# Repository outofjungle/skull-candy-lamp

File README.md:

# Skull Candy Lamp

Replacement guts for the [Cute Skull Lamp](https://www.printables.com/model/40977-cute-skull-lamp).

## Front

## Back

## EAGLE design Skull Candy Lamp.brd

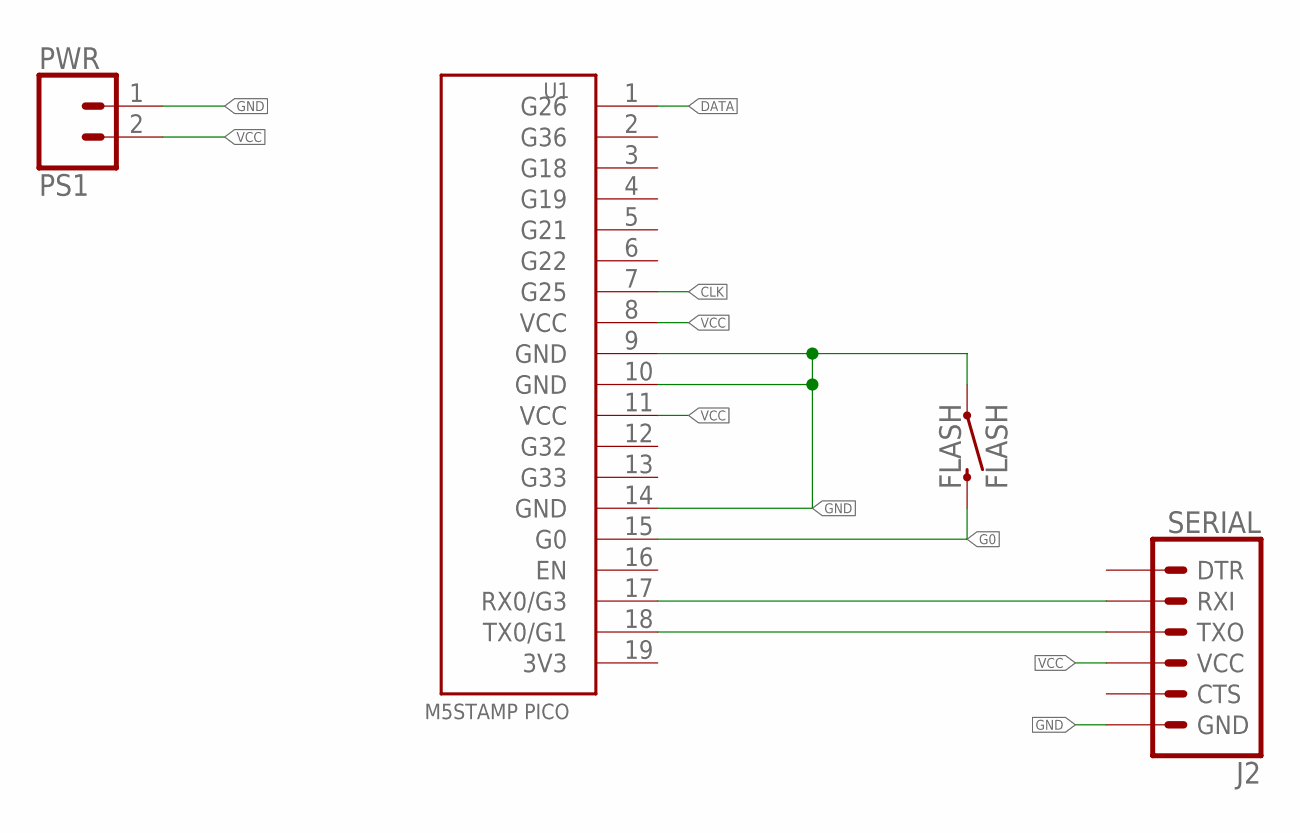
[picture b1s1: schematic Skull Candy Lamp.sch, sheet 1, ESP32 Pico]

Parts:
FLASH: FLASH; TACTILE_SWITCH_SMD_5.2MM
J2: SERIAL; 6_PIN_SERIAL_TARGET_SIDE_W_SILK
PS1: PWR; MOLEX-1X2_LOCK
U1: M5STAMP PICO; M5STAMP-PICO

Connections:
3V3: U1.19 (3V3)
CLK: U1.7 (G25); also elsewhere on the board
DATA: U1.1 (G26); also elsewhere on the board
G0: FLASH.3 (2), U1.15 (G0)
GND: FLASH.1, J2.P$6 (GND), PS1.1, U1.9 (GND), U1.10 (GND), U1.14 (GND); also elsewhere on the board
RX: J2.P$3 (RXI), U1.17 (RX0/G3)
TX: J2.P$2 (TXO), U1.18 (TX0/G1)
VCC: J2.P$4 (VCC), PS1.2, U1.8 (VCC), U1.11 (VCC); also elsewhere on the board

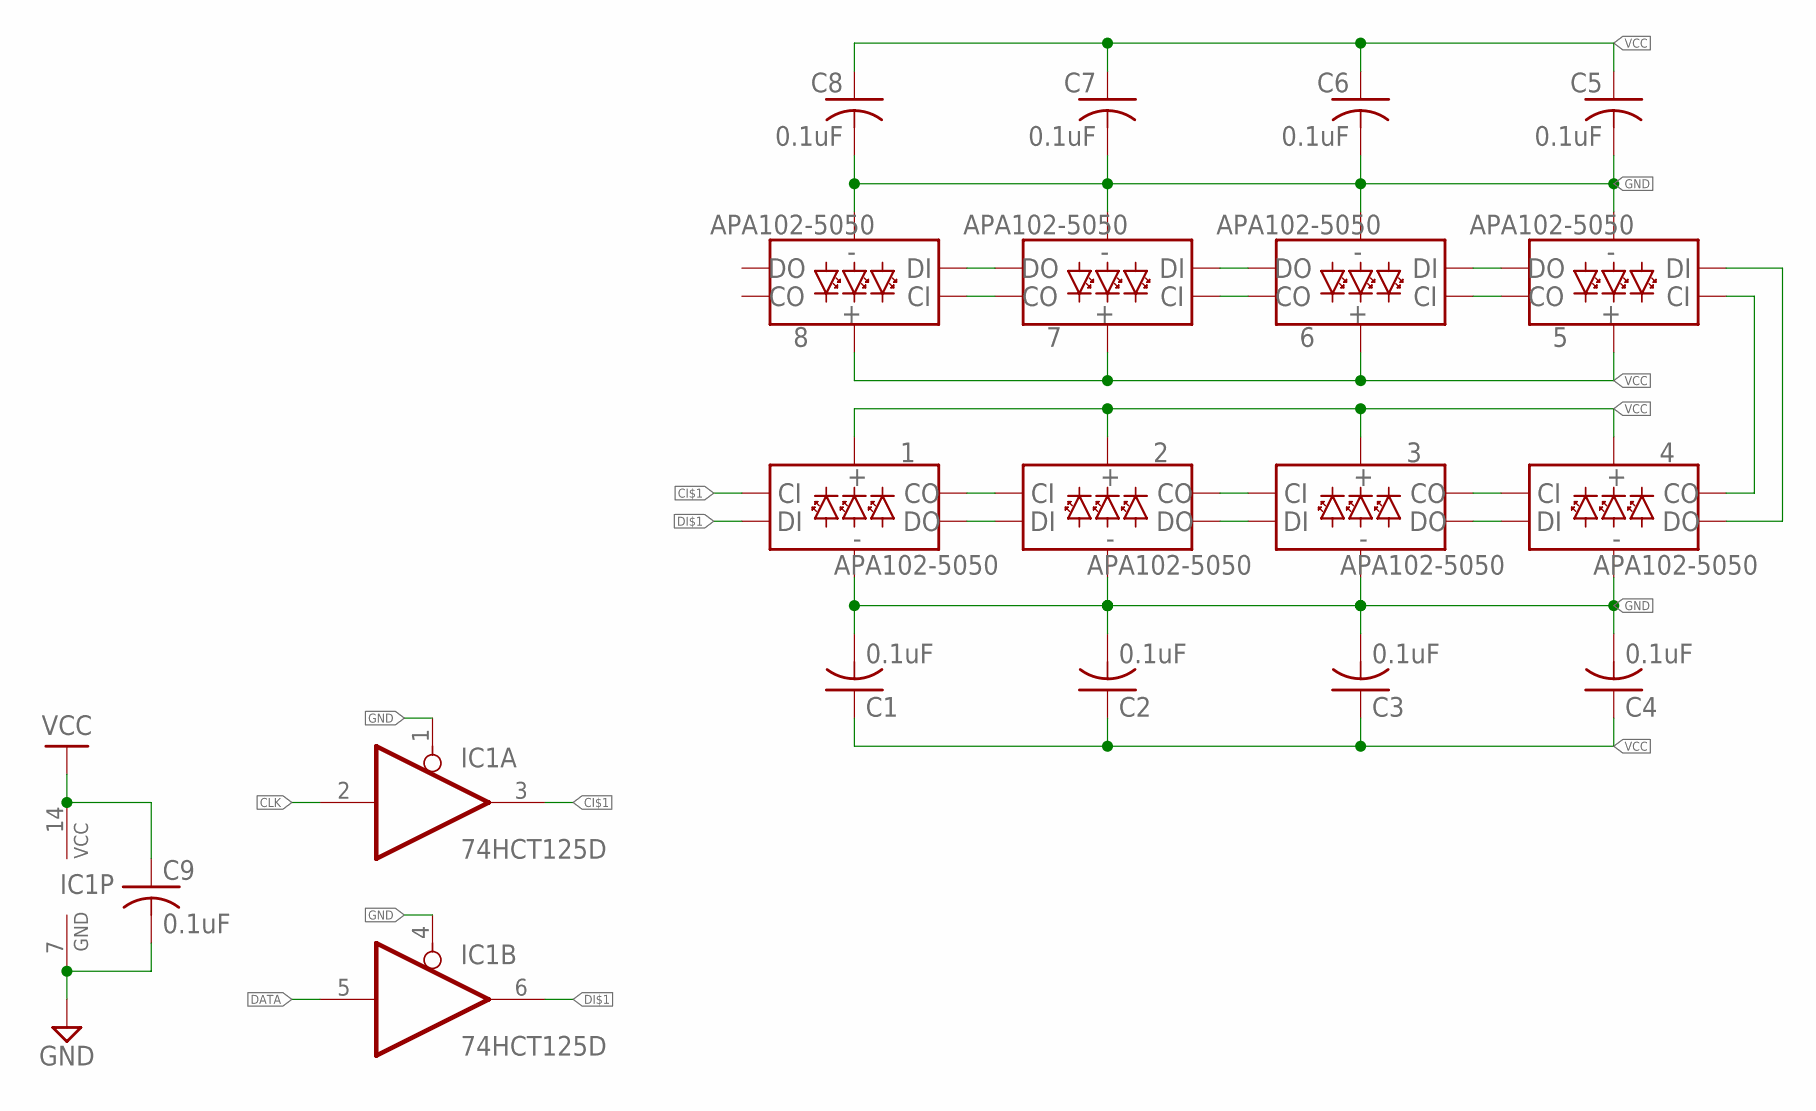
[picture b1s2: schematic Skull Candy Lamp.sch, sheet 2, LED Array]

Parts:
1, 2, 3, 4, 5, 6, 7, 8: APA102-5050
C1, C2, C3, C4, C5, C6, C7, C8, C9: 0.1uF; CAPC2012X110
IC1: 74HCT125D; SO14

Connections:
CI$1: 1.P2 (CI), IC1.3 (O)
CI$2: 1.P5 (CO), 2.P2 (CI)
CI$3: 2.P5 (CO), 3.P2 (CI)
CI$4: 3.P5 (CO), 4.P2 (CI)
CI$5: 4.P5 (CO), 5.P2 (CI)
CI$6: 5.P5 (CO), 6.P2 (CI)
CI$7: 6.P5 (CO), 7.P2 (CI)
CI$8: 7.P5 (CO), 8.P2 (CI)
CLK: IC1.2 (I); also elsewhere on the board
DATA: IC1.5 (I); also elsewhere on the board
DI$1: 1.P1 (DI), IC1.6 (O)
DI$2: 1.P6 (DO), 2.P1 (DI)
DI$3: 2.P6 (DO), 3.P1 (DI)
DI$4: 3.P6 (DO), 4.P1 (DI)
DI$5: 4.P6 (DO), 5.P1 (DI)
DI$6: 5.P6 (DO), 6.P1 (DI)
DI$7: 6.P6 (DO), 7.P1 (DI)
DI$8: 7.P6 (DO), 8.P1 (DI)
GND: 1.P3 (GND), 2.P3 (GND), 3.P3 (GND), 4.P3 (GND), 5.P3 (GND), 6.P3 (GND), 7.P3 (GND), 8.P3 (GND), C1.2, C2.2, C3.2, C4.2, C5.2, C6.2, C7.2, C8.2, C9.2, IC1.1 (OE), IC1.4 (OE), IC1.7 (GND); also elsewhere on the board
VCC: 1.P4 (VCC), 2.P4 (VCC), 3.P4 (VCC), 4.P4 (VCC), 5.P4 (VCC), 6.P4 (VCC), 7.P4 (VCC), 8.P4 (VCC), C1.1, C2.1, C3.1, C4.1, C5.1, C6.1, C7.1, C8.1, C9.1, IC1.14 (VCC); also elsewhere on the board

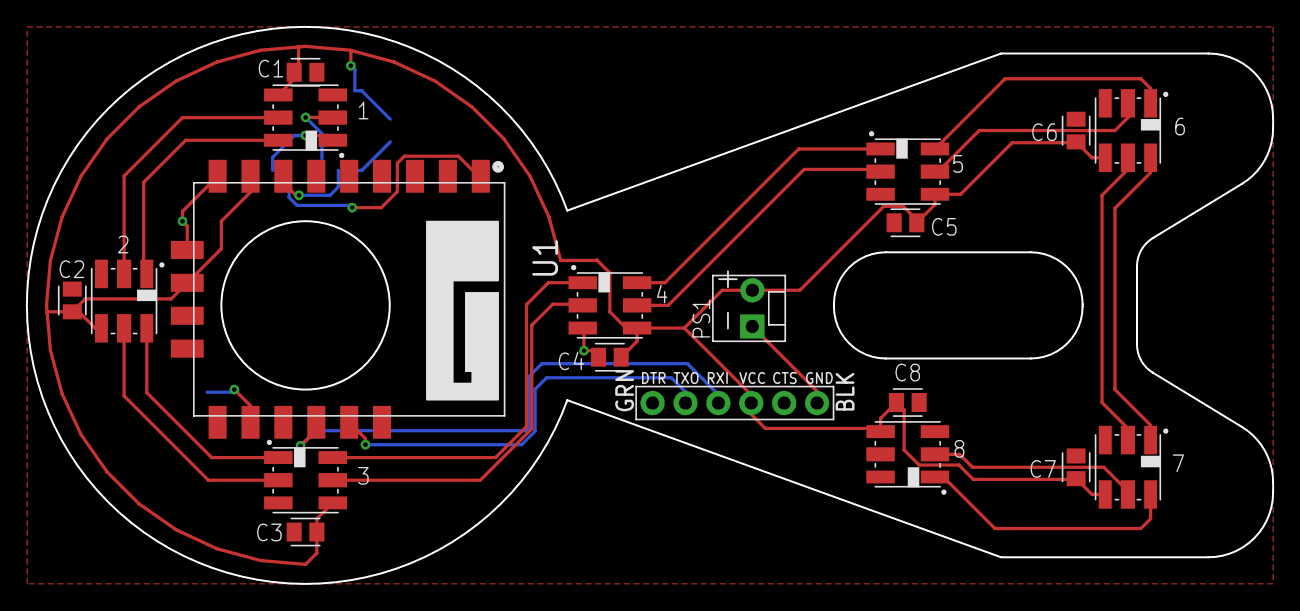
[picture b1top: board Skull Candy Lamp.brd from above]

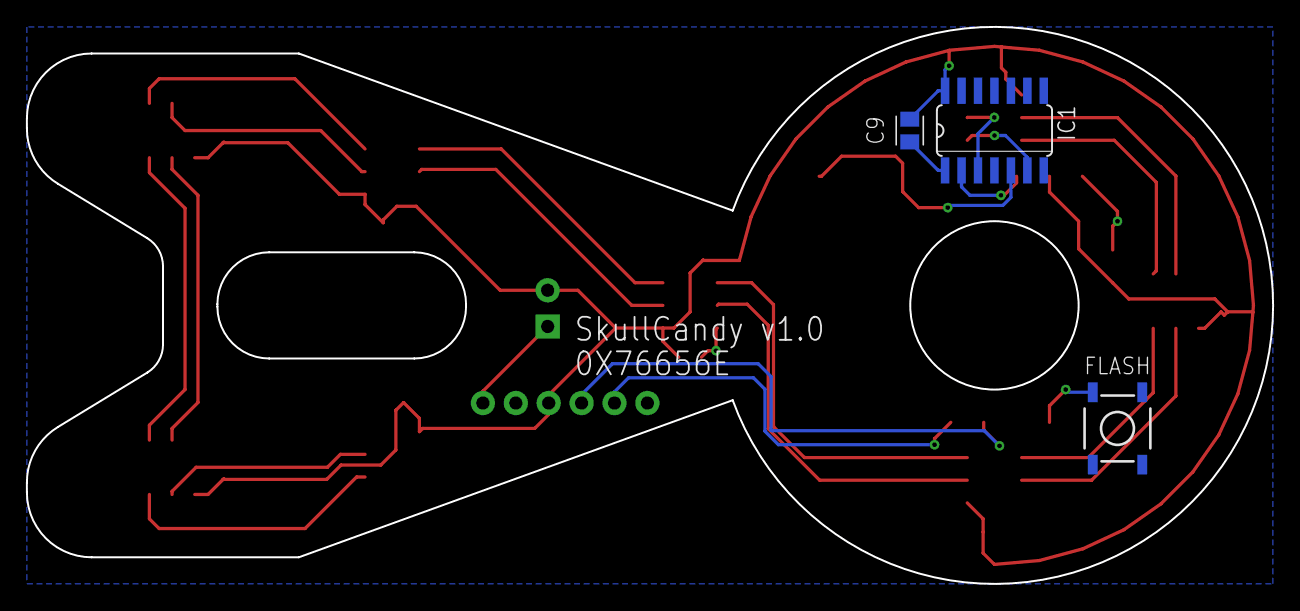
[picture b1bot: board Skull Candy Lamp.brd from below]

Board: 2 copper layers, 96.2 x 43.0 mm, 22 parts (3 on the bottom side), 23 nets.

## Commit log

2022-09-28 cosmetic updates
2022-09-28 adding pcb images

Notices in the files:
parts and their libraries:
SparkFun-LED: Licensing: Creative Commons ShareAlike 4.0 International - https://creativecommons.org/licenses/by-sa/4.0
